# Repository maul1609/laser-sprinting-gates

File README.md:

# Laser Sprinting Gates

This Laser Sprinting Gate (LSG) project uses two Arduino Nanos and an Arduino Uno linked together via 
nRF24l01 modules. 

<em>The Laser Speed Gates - Indoors.</em>

# Table of contents
1. [Overview](#overview)
2. [Remote control](#rem-cont)
3. [Detectors](#detectors)
4. [Dependencies](#Dependencies)
5. [Folder structure](#Folder-Structure)
6. [Contributing](#Contributing)
7. [Code of Conduct](#Code-of-Conduct)

## Overview 

The electronics fits in their own project boxes, which are 3-d printed.

There are two boxes for the laser diodes, two for the detectors / transceivers; and one for the remote control.

You set up the tripods, point the lasers into the detectors a measured distance apart and switch everything on.

Then press the pushbutton on the remote control. The LCD will say "Ready" if the laser gates are closed, or will tell you to "Close gates" if the lasers are not directed on the photodiodes.

When you run through both gates the remote control will display your time on the LCD in <b>min:sec:ms</b> format.

## Remote Control 
The remote control is operated as a "master" to two "slaves" (the detectors). When the reset button is pressed a signal is sent to the two slaves, which send a return packet using the AckPayload protocol. The signal from the master includes the time in milli-seconds when the signal is sent (which is the reference time).

The information in the return packet includes information on whether the gates are closed (i.e. laser pointing at the photodiode); the reference time; and the time at which the gate was first opened (laser beam broken) after the reset signal. If both gates have been opened the difference between these two times is the time taken. This time is then printed to the remote control LCD.

The LCD uses the LiquidCrystal library and the following code to interface to it:

<code>
LiquidCrystal lcd(1,0,5,4,3,2);
</code>

However, this may change so that the master uses pin 2 or 3 for the reset button (as an interupt can then be attached).

The remote control enclosure is 3-D printed (designs are part of this repository).

<em>The remote control consists of an Arduino Uno; nRF24L01 transceiver module; reset button; and LCD screen.</em>

Upload the master.ino to the arduino UNO.

## Detectors 
The detectors both use an Arduino Nano; nRF24L01 modules. The pins used on the Nano (same for the Uno board used in the remote control) are:

<table style="width:100%">
  <tr> 
    <td>
    Arduino Pin <br>
    </td>
    <td>
    nRF24L01 Pin
    </td>
  </tr>
  <tr> 
    <td>
    3.3V <br>
    </td>
    <td>
    VCC
    </td>
  </tr>
  <tr> 
    <td>
    GND <br>
    </td>
    <td>
    GND
    </td>
  </tr>
  <tr> 
    <td>
    8 <br>
    </td>
    <td>
    CSN
    </td>
  </tr>
  <tr> 
    <td>
    7 <br>
    </td>
    <td>
    CE
    </td>
  </tr>
  <tr> 
    <td>
    13 <br>
    </td>
    <td>
    SCK
    </td>
  </tr>
  <tr> 
    <td>
    11 <br>
    </td>
    <td>
    MOSI
    </td>
  </tr>
  <tr> 
    <td>
    12 <br>
    </td>
    <td>
    MISO
    </td>
  </tr>
</table>

There is also an interface to a photodiode circuit (a photodiode, two resistors and a p-type transistor), which goes to pin 2.

The photodiode circuit used is taken from Figure 3, using circuit A, with RBE=1 kohm, RL=10 kohm and a BD140 (p-type) transistor [see here](reference/Photodiode_circuit.pdf).

<em>Two detector boards being constructed.</em>

Upload the slaves.ino to the Arduino Nanos: one should have 

<code>thisSlaveAddress set to RxAAA</code> 

and the other

<code>thisSlaveAddress set to RxAAB</code> 

(change the address on approximate line 12 / 13 or the slaves.ino file).

## Dependencies 

I needed to install two libraries for the Arduino for communication. The libraries are nRF24L01 and RF24.

## Folder structure 

The repository structure is now discussed

### Directory layout

    .                           
    ├── arduino               # code for the Arduino
    ├── images                # image files for the project
    ├── links                 # some links that I used 
    ├── openSCAD              # Design files in openSCAD
    ├── README.md             # This readme
    └── reference			  # contains reference documents
    
----------

**REQUIRED PARTS**

In order to **make your own Laser Sprinting Gates**, you may use the **part list below** to acquire all the components **on your own**.

<table style="width:100%">
  <tr>
    <td>
    Arduino Uno <br>
    </td>
    <td><a href="https://www.amazon.co.uk/Arduino-ATMega16U2-ATMEGA328P-Microcontroller-Official/dp/B077JMX1NP/ref=sr_1_9?s=computers&ie=UTF8&qid=1531612973&sr=1-9&keywords=arduino+uno" target="_blank"> Amazon </a></td> 
    <td>£20</td>
  </tr>

  <tr>
    <td>
    Arduino Nano A000005 Board V3 x2<br>
    </td>
    <td><a href="https://www.rapidonline.com/arduino-nano-a000005-board-v3-73-4448" target="_blank"> Rapid Electronics </a></td> 
    <td>£15.60 x 2 = £31.20</td>
  </tr>

  <tr>
    <td>
    Strip board <br>
    </td>
    <td><a href="https://www.amazon.co.uk/gp/product/B072PS947V/ref=oh_aui_detailpage_o09_s00?ie=UTF8&psc=1" target="_blank"> Amazon </a></td> 
    <td>£10</td>
  </tr>

  <tr>
    <td>
    Slide switch <br>
    </td>
    <td><a href="https://www.amazon.co.uk/gp/product/B008R50AA0/ref=oh_aui_detailpage_o07_s00?ie=UTF8&psc=1" target="_blank"> Amazon </a></td> 
    <td>£0.15</td>
  </tr>
  
  <tr>
    <td>
    PCB Header Connectors <br>
    </td>
    <td><a href="https://www.amazon.co.uk/gp/product/B01M69EA9O/ref=oh_aui_detailpage_o03_s00?ie=UTF8&psc=1" target="_blank"> Amazon </a></td> 
    <td>£5</td>
  </tr>

  <tr>
    <td>
    Affix Pozi Pan Head Stainless Steel Screws M2.5 12mm  <br>
    </td>
    <td><a href="https://www.rapidonline.com/Affix-Pozi-Pan-Head-Stainless-Steel-Screws-M2-5-12mm-Pack-Of-100-33-4205?utm_source=AffWin&utm_medium=Affiliate&awc=1799_1531559350_6bf53c34df454762e1e501399281f666" target="_blank"> Rapid online </a></td> 
    <td>£3.40</td>
  </tr>
  
  <tr>
    <td>
    Affix Stainless Steel Plain Washers M2.5  <br>
    </td>
    <td><a href="https://www.rapidonline.com/affix-stainless-steel-plain-washers-m2-5-pack-of-100-33-4315" target="_blank"> Rapid online </a></td> 
    <td>£1</td>
  </tr>
  
  <tr>
    <td>
    M2.5 nuts <br>
    </td>
    <td><a href="https://www.rapidonline.com/tr-fastenings-w-m2-5-hfst-tc1-steel-full-nuts-metric-m2-5-box-of-100-33-6589" target="_blank"> Rapid online </a></td> 
    <td>£1.20</td>
  </tr>

  <tr>
    <td>
    10 Metres 4mm Brown Sleeving On A Roll. <br>
    </td>
    <td><a href="https://www.amazon.co.uk/gp/product/B006I1K7NU/ref=oh_aui_search_detailpage?ie=UTF8&psc=1" target="_blank"> Amazon </a></td> 
    <td>£2.99</td>
  </tr>
  
  <tr>
    <td>
    LED <br>
    </td>
    <td><a href="https://www.amazon.co.uk/dp/B00CM5DEZO/ref=sxts_kp_lp_3?pf_rd_m=A3P5ROKL5A1OLE&pf_rd_p=fb7bbe16-4a21-4f5a-938c-e2ac1558fbcd&pd_rd_wg=WvUCM&pf_rd_r=G8N068HW8BDFM7DW6CEY&pf_rd_s=desktop-sx-top-slot&pf_rd_t=301&pd_rd_i=B00CM5DEZO&pd_rd_w=RxAWr&pf_rd_i=leds&pd_rd_r=ad3598ab-370e-4f6e-a6e7-f164199962c9&ie=UTF8&qid=1535959984&sr=3" target="_blank"> Amazon </a></td> 
    <td>£0.65</td>
  </tr>

  <tr>
    <td>
    Linear regulator <br>
    </td>
    <td><a href="https://www.amazon.co.uk/LM338T-Adjustable-Positive-Voltage-Regulator/dp/B07F2YMXTR/ref=sr_1_cc_1?s=aps&ie=UTF8&qid=1531560057&sr=1-1-catcorr&keywords=lm338" target="_blank"> Amazon </a></td> 
    <td>£3</td>
  </tr>

  <tr>
    <td>
    nRF24L01 module <br>
    </td>
    <td><a href="https://www.amazon.co.uk/gp/product/B06WD17WLS/ref=oh_aui_detailpage_o08_s00?ie=UTF8&psc=1"> Amazon </a></td> 
    <td>£13.99</td>
  </tr>

  <tr>
    <td>
    photodiodes <br>
    </td>
    <td><a href="https://www.amazon.co.uk/gp/product/B00M1PMHO4/ref=oh_aui_detailpage_o08_s01?ie=UTF8&psc=1"> Amazon </a></td> 
    <td>£2.99</td>
  </tr>
  
  <tr>
    <td>
    Laser diodes <br>
    </td>
    <td><a href="https://www.amazon.co.uk/gp/product/B0798PXGTS/ref=oh_aui_detailpage_o08_s02?ie=UTF8&psc=1"> Amazon </a></td> 
    <td>£3.99</td>
  </tr>

  <tr>
    <td>
    LCD <br>
    </td>
    <td><a href="https://www.rapidonline.com/winstar-wh1602b-tmi-jt-16x2-lcd-display-blue-negative-mode-white-led-backlight-57-2228"> Rapid electronics </a></td> 
    <td>£6.40</td>
  </tr>

  <tr>
    <td>
    Pushbutton switch <br>
    </td>
    <td><a href="https://www.amazon.co.uk/gp/product/B00KHV7QFE/ref=oh_aui_detailpage_o01_s00?ie=UTF8&psc=1" target="_blank"> Amazon </a></td> 
    <td>£2.22</td>
  </tr>
	
  <tr>
    <td>
    9V battery clip connector <br>
    </td>
    <td><a href="https://www.amazon.co.uk/gp/product/B00HG8BJWM/ref=oh_aui_search_detailpage?ie=UTF8&psc=1" target="_blank"> Amazon </a></td> 
    <td>£0.87</td>
  </tr>
	
  <tr>
    <td>
    M2x50mm screws (cut to size) <br>
    </td>
    <td><a href="https://www.amazon.co.uk/Stainless-Steel-Phillips-Round-Screws/dp/B01EZZFBDG/ref=sr_1_2?ie=UTF8&qid=1540222929&sr=8-2&keywords=m2+x+50mm+304" target="_blank"> Amazon </a></td> 
    <td>£14.35</td>
  </tr>
	
  <tr>
    <td>
    Tripod Socket <br>
    </td>
    <td><a href="https://www.amazon.co.uk/Hillman-Group-2511-4-20-13-Pack/dp/B00HYLZ33W/ref=sr_1_1?s=electronics&ie=UTF8&qid=1516292925&sr=8-1&keywords=Brad+Hole+Tee+Nuts"> Amazon </a></td> 
    <td>£10</td>
  </tr>
	
  <tr>
    <td>
    m2 counter sunk <br>
    </td>
    <td><a href="https://www.ettinger.de/en/product/0112138"> Ettinger or similar supplier </a></td> 
    <td>£3</td>
  </tr>
	
  <tr>
    <td>
    Hex Standoff Male/Female BSB-2010E, 10mm, M2 x M2 <br>
    </td>
    <td><a href="https://uk.rs-online.com/web/p/standoffs/6643035/?relevancy-data=636F3D3126696E3D4931384E525353746F636B4E756D626572266C753D656E266D6D3D6D61746368616C6C26706D3D5E2828282872737C5253295B205D3F293F285C647B337D5B5C2D5C735D3F5C647B332C347D5B705061415D3F29297C283235285C647B387D7C5C647B317D5C2D5C647B377D2929292426706F3D3126736E3D592673723D2673743D52535F53544F434B5F4E554D4245522677633D4E4F4E45267573743D36363433303335267374613D3636343330333526&searchHistory=%7B%22enabled%22%3Afalse%7D"> RS </a></td> 
    <td>£7</td>
  </tr>

  <tr>
    <td>
    Hexagon Nut D934 M2 <br>
    </td>
    <td><a href="https://www.ettinger.de/en/product/0210011"> Ettinger or similar supplier </a></td> 
    <td>£2</td>
  </tr>
	
  <tr>
    <td>
    BD140 <br>
    </td>
    <td><a href="https://www.amazon.co.uk/BD140-10-CDI-Transistor-Bipolar-1-5A-TO126/dp/B07HR3BWLZ/ref=sr_1_2?ie=UTF8&qid=1540224481&sr=8-2&keywords=bd140"> Amazon </a></td> 
    <td>£3.50</td>
  </tr>

</table>

Plus: 
<ul>
<li> Resistors: 1k &Omega; ;2x220 &Omega; ;10 k &Omega;
<li> some other wire 22awg for low current connections;  
<li> Heat shrink for 22awg wire.
<li> 4 x 9V batteries
<li> 4x tripod stands. Good quality is obviously better, but you can get them quite cheap of ebay see <a href="https://www.ebay.co.uk/itm/Stretchable-Camera-Tripod-Stand-Mount-Holder-for-iPhone-8-7-Plus-Samsung-Phone/362434198720?_trkparms=aid%3D111001%26algo%3DREC.SEED%26ao%3D1%26asc%3D20160908105057%26meid%3Dc3250a39280f44349835c781bb6ad9ca%26pid%3D100675%26rk%3D7%26rkt%3D15%26sd%3D391719322779%26itm%3D362434198720&_trksid=p2481888.c100675.m4236&_trkparms=pageci%3A2dd86933-d613-11e8-b9b5-74dbd1801eb4%7Cparentrq%3A9c7ed44a1660ab4dc137dc5cfff6aee7%7Ciid%3A1"> here </a>
<li> 3-d printing materials:
	<ul>
	<li> PLA plastic
	</ul>
</ul>

## Contributing

Contributions to this Laser Sprinting Gate project are more than welcome. I am sure there are many improvements that could be made. I am very happy to discuss ideas for improvement and how to add/remove features.  

Please use the issue tracker at https://github.com/maul1609/laser-sprinting-gates/issues if you want to notify me of an issue or need support. If you want to contribute, please either create an issue or make a pull request. Alternatively, come and see me in Manchester and/or lets meet for a coffee and a chat!

## Code of Conduct

To be arranged.

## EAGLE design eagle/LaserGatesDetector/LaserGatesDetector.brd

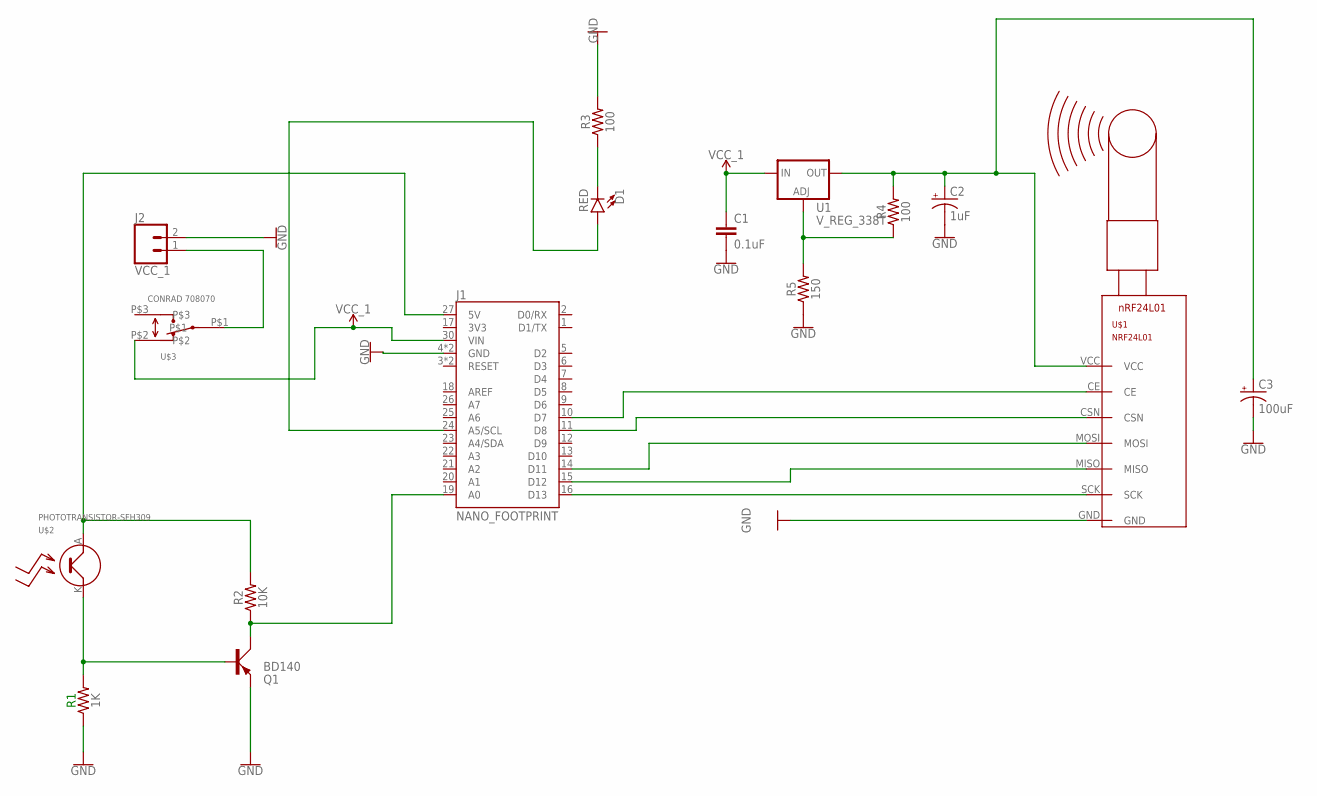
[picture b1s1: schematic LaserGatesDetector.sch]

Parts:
C1: 0.1uF; CAP-PTH-SMALL-KIT
C2: 1uF; CPOL-RADIAL-2.5MM-5MM
C3: 100uF; CPOL-RADIAL-5MM-10MM
D1: RED; LED_5MM-KIT
J1: NANO_FOOTPRINT; NANO
J2: VCC_1; 1X02
Q1: BD140; TO126AV
R1: 1K; AXIAL-0.3
R2: 10K; AXIAL-0.3
R3, R4: 100; AXIAL-0.3
R5: 150; AXIAL-0.3
U1: V_REG_338T; TO220-ADJ
U$1: NRF24L01
U$2: PHOTOTRANSISTOR-SFH309; SFH
U$3: SLIDE-SWITCH-CONRAD708070

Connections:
GND: C1.2, C2.2 (-), C3.-, J1.4 (GND), J1.29 (GND), J2.2, Q1.E, R1.P$1 (1), R3.P$2 (2), R5.P$1 (1), U$1.GND
unnamed: J1.11 (D8), U$1.CSN
unnamed: J1.10 (D7), U$1.CE
unnamed: J1.16 (D13), U$1.SCK
unnamed: J1.14 (D11), U$1.MOSI
unnamed: J1.15 (D12), U$1.MISO
unnamed: Q1.B, R1.P$2 (2), U$2.K
unnamed: D1.A, J1.24 (A5/SCL)
unnamed: D1.K (C), R3.P$1 (1)
unnamed: J2.1, U$3.P$1
unnamed: J1.27 (5V), R2.P$2 (2), U$2.A
unnamed: J1.19 (A0), Q1.C, R2.P$1 (1)
unnamed: R4.P$1 (1), R5.P$2 (2), U1.ADJ
unnamed: C2.1 (+), C3.+, R4.P$2 (2), U1.OUT, U$1.VCC
VCC_1: C1.1, J1.30 (VIN), U1.IN, U$3.P$2

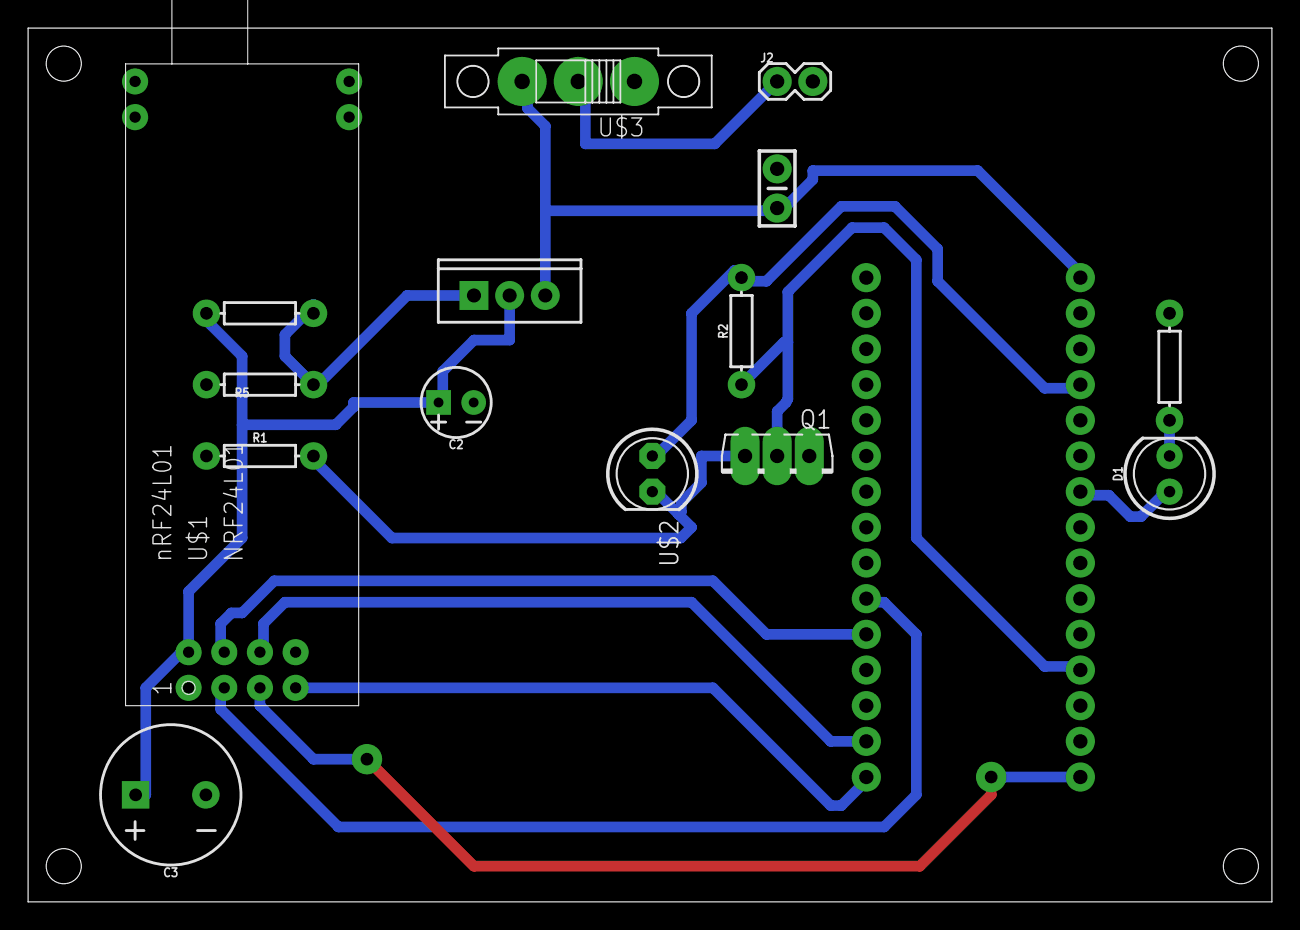
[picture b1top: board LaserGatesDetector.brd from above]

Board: 2 copper layers, 88.6 x 62.2 mm, 16 parts (0 on the bottom side), 15 nets.

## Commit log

2018-10-22 Create LICENSE
2020-09-08 reduced light threshold to try to mitigate sunlight
2021-07-04 added PCB board designs, improved laser enclosure box for charging, etc
2023-04-30 updates and bug fixes

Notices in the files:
parts and their libraries:
SparkFun-Capacitors: Licensing: Creative Commons ShareAlike 4.0 International - https://creativecommons.org/licenses/by-sa/4.0
